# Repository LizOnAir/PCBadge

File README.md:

# Soup

Mini Soup being smack onto a PCB.

## Schematic:

## PCB layout:

made in Kicad by Liz.

## BOM:

|Designator|Footprint                |Quantity|Value   |LCSC Part #|
|----------|-------------------------|--------|--------|-----------|
|C1        |0402                     |1       |220nF   |           |
|D3, D4    |0402                     |2       |LED     |C23182     |
|L1        |Antenna_8500000x5500000mm|1       |L       |           |
|R1, R2    |0402                     |2       |47      |C16772     |
|U2        |NT3H2111W0FHKH           |1       |13.56MHz|C710403    |

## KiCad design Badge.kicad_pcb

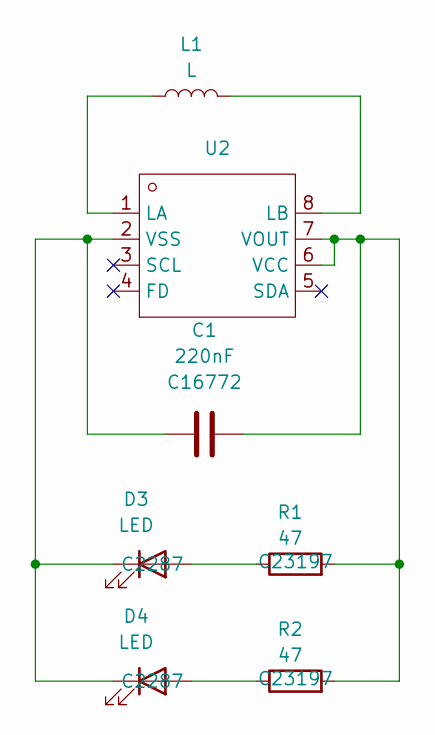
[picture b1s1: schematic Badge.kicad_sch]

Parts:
C1: 220nF; C_0402_1005Metric
D3, D4: LED; LED_0402_1005Metric_Pad0.77x0.64mm_HandSolder
L1: L; Antenna_8500000x5500000mm
R1, R2: 47; R_0402_1005Metric
U2: 13.56MHz; NT3H2111W0FHKH; Manufacturer Part NT3H2111W0FHKH; LCSC Part Name NT3H2111W0FHKH

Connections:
unnamed: D3.2 (A), R1.1
unnamed: C1.1, D3.1 (K), D4.1 (K), U2.2 (VSS)
unnamed: D4.2 (A), R2.1
unnamed: L1.1, U2.1 (LA)
unnamed: L1.2, U2.8 (LB)
unnamed: C1.2, R1.2, R2.2, U2.6 (VCC), U2.7 (VOUT)

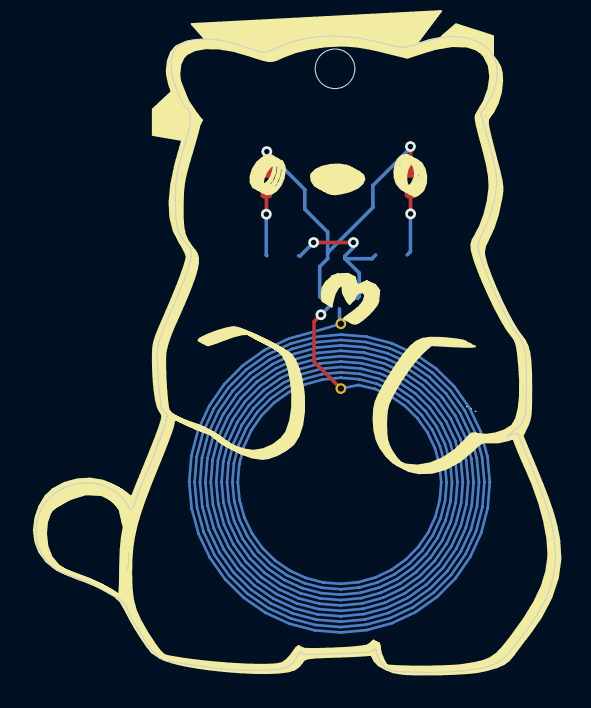
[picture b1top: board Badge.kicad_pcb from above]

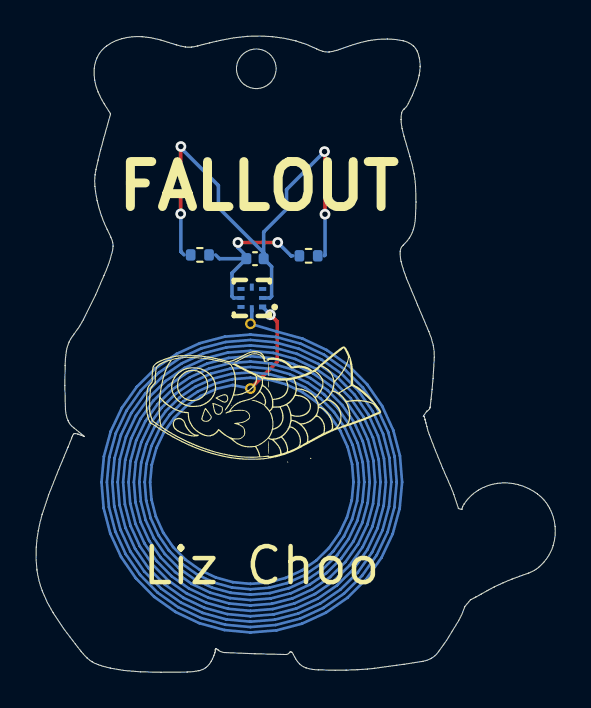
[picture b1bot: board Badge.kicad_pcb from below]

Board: 2 copper layers, 28.8 x 35.3 mm, 7 parts (5 on the bottom side), 6 nets.

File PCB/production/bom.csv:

Designator,Footprint,Quantity,Value,LCSC Part #
C1,0402,1,220nF,
"D3, D4",0402,2,LED,
L1,Antenna_8500000x5500000mm,1,L,
"R1, R2",0402,2,47,
U2,NT3H2111W0FHKH,1,13.56MHz,C710403
